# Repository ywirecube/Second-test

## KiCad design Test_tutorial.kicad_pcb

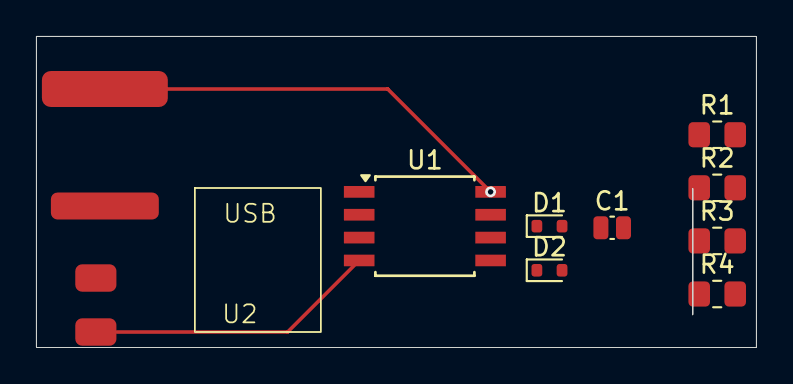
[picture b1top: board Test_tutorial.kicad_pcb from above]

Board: 2 copper layers, 40.0 x 17.3 mm, 9 parts (0 on the bottom side), 7 nets.

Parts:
C1: 100n; C_0504_1310Metric_Pad0.83x1.28mm_HandSolder
D1, D2: 3V6; D_SOD-523
R1, R2, R3, R4: 68R; R_0805_2012Metric_Pad1.20x1.40mm_HandSolder
U1: ATtiny45-20S; SOIC-8W_5.3x5.3mm_P1.27mm
U2: PCB_uSB_connector

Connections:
+5V: C1.1, R4.1, U1.8 (VCC), U2.1 (Vcc)
GND: C1.2, D1.2 (A), D2.2 (A), U1.4 (GND), U2.4 (GND)
unnamed: D1.1 (K), R3.1, U2.2 (D++)
unnamed: D2.1 (K), R2.1, R4.2, U2.3 (D--)
unnamed: R1.2, U1.5 (AREF/PB0)
unnamed: R2.2, U1.7 (PB2)
unnamed: R3.2, U1.3 (XTAL2/PB4)

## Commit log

2024-04-05 schauma mal obs jetzt nochmal geht
2024-04-05 zum öffnen
2024-04-12 added README
2024-04-12 added Testdokument
2024-04-12 test
2024-04-12 geklonter Testordner
2024-04-12 test2, inventhub -> local
2024-04-12 deleted: README.md deleted: Testdokument.txt deleted: Testfile2.txt deleted: Testprojekt_1 deleted: Todo.txt
2024-04-12 new file
